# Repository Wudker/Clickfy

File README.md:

# Clickfy – BLE Multimedia Remote

Clickfy is a compact, keychain-sized multimedia remote based on the ESP32-C3. It communicates through the BLE HID profile and provides dedicated controls for play/pause, next track and previous track. A custom PCB integrates the control buttons, Li-Po battery, status LED and battery-voltage monitoring circuit. The firmware uses sleep modes to reduce power consumption, with development focused on minimizing wake-up and BLE reconnection times.

## Technologies

`ESP32-C3` `C/C++` `Bluetooth Low Energy` `BLE HID` `Li-Po battery` `ADC battery monitoring` `Custom PCB` `Low-power operation`

## Usage and development status

After powering on the device, pair Clickfy with a phone, computer or another BLE-compatible media device and use the three buttons to control playback. The current prototype has been built and tested. Planned improvements include further power optimization, shorter reconnection times and support for additional multimedia functions.

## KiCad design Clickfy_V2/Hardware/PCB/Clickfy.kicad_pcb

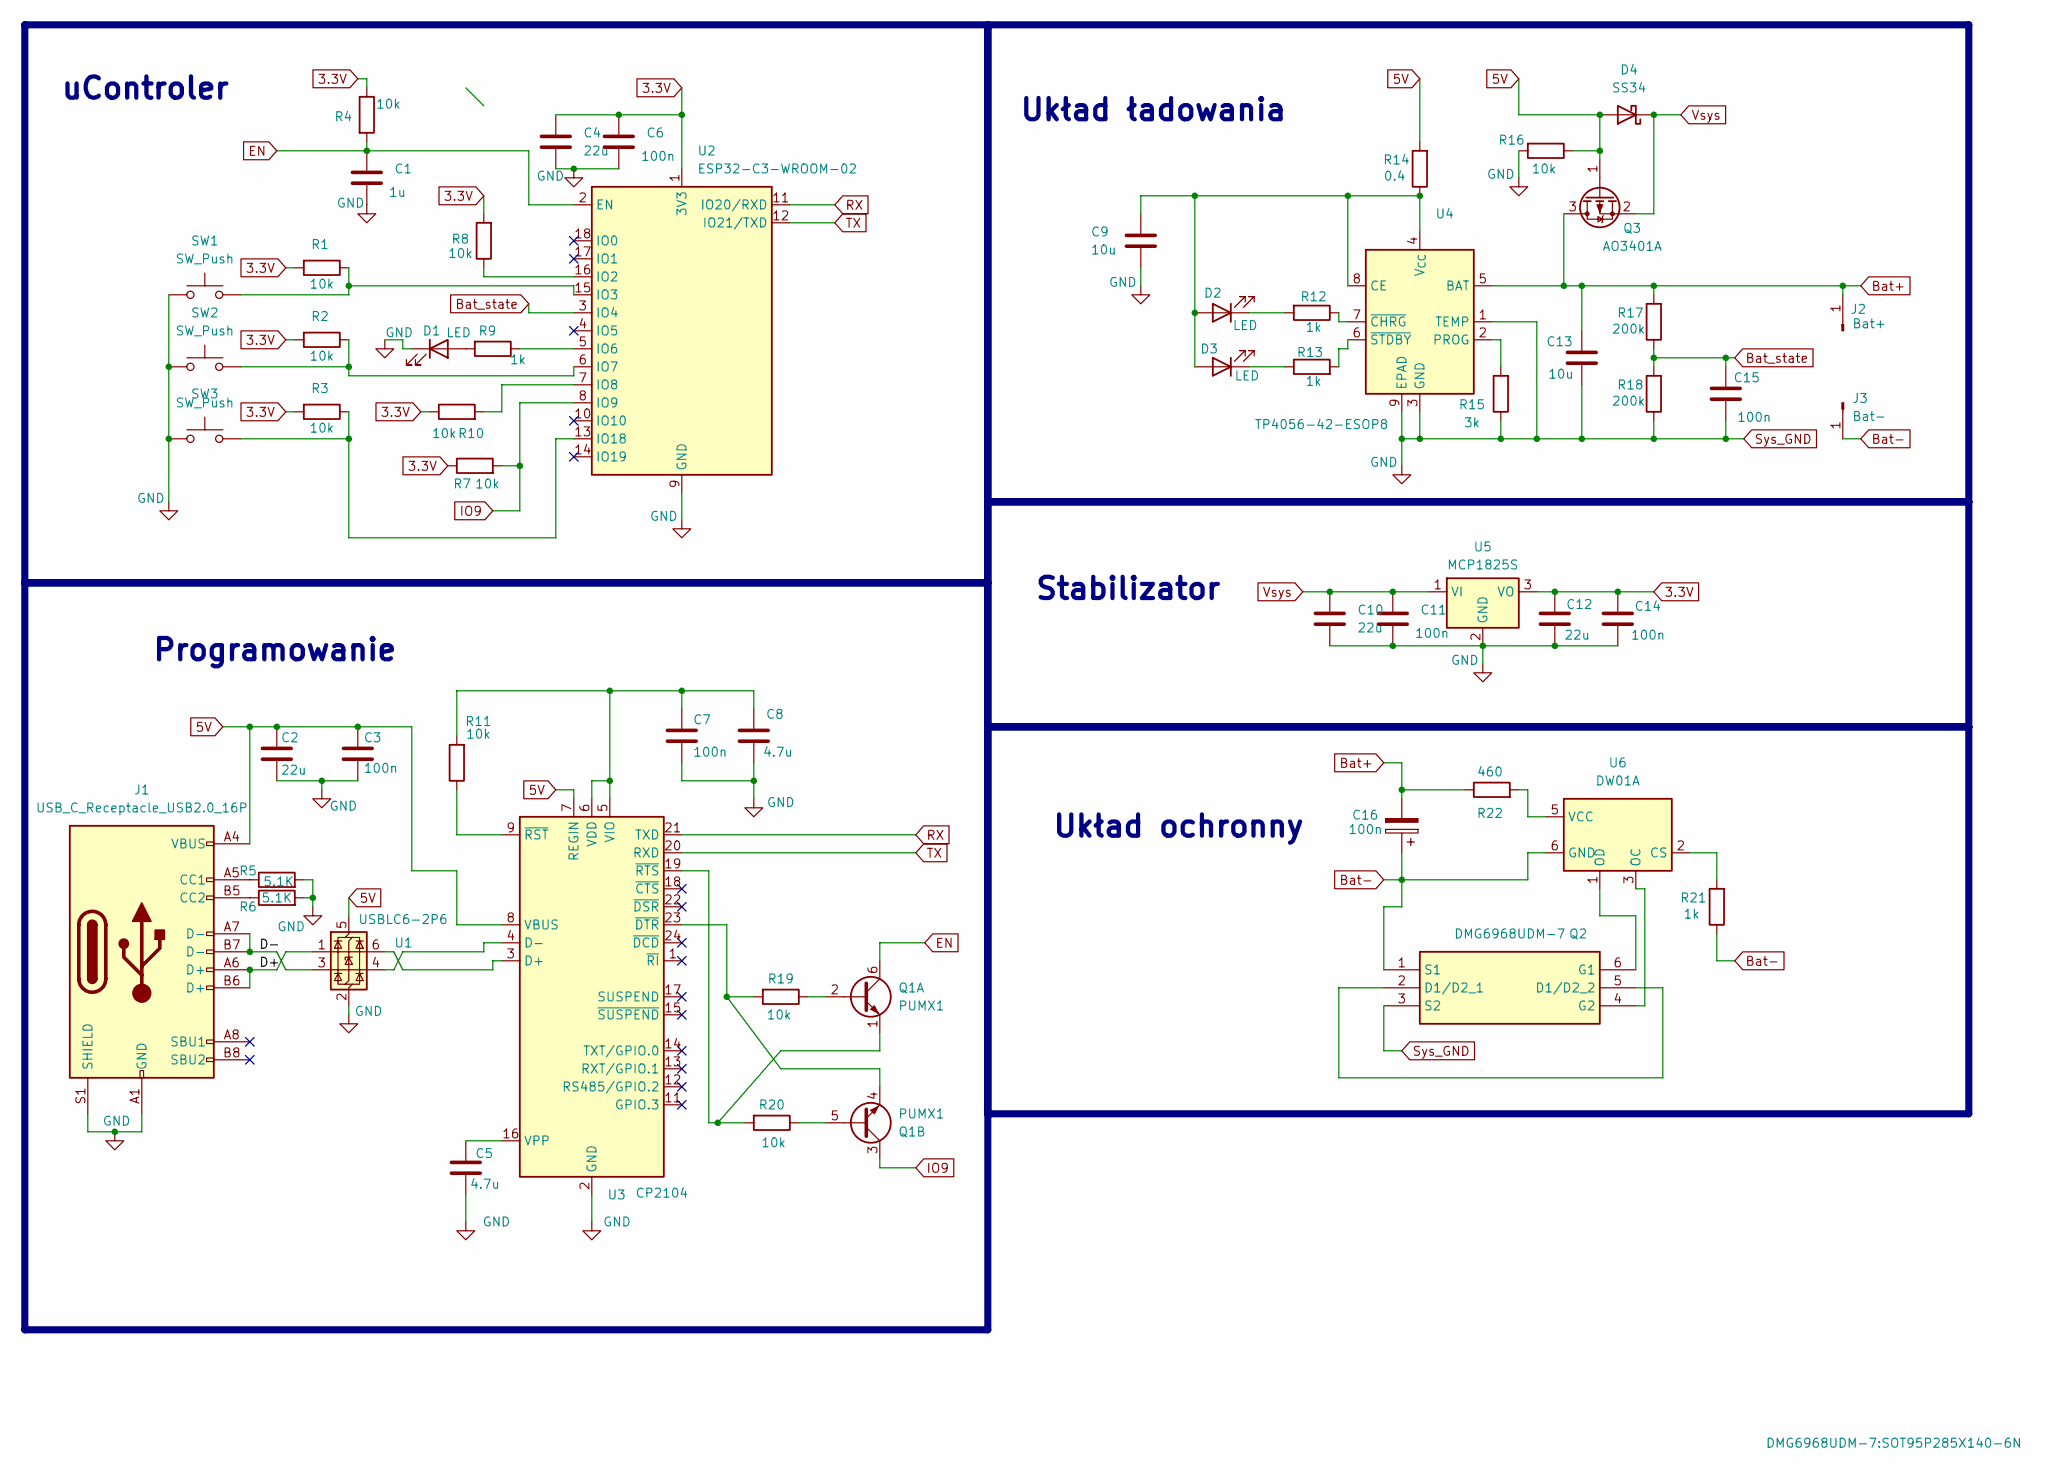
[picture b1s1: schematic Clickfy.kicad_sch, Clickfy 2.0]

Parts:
C1: 1u; C_1206_3216Metric
C2, C4, C10, C12: 22u; C_1206_3216Metric
C3, C6, C7, C11, C14, C15, C16: 100n; C_1206_3216Metric
C5, C8: 4.7u; C_1206_3216Metric
C9, C13: 10u; C_1206_3216Metric
D1: LED; LED_D3.0mm
D2, D3: LED; LED_1206_3216Metric
D4: SS34; D_SMC
J1: USB_C_Receptacle_USB2.0_16P; USB_C_Receptacle_GCT_USB4105-xx-A_16P_TopMnt_Horizontal
J2: Bat+; SolderWire-0.1sqmm_1x01_D0.4mm_OD1mm
J3: Bat-; SolderWire-0.1sqmm_1x01_D0.4mm_OD1mm
Q1: PUMX1; SOT-363_SC-70-6
Q2: DMG6968UDM-7; SOT95P285X140-6N; Manufacturer_Part_Number DMG6968UDM-7
Q3: AO3401A; SOT-23
R1, R2, R3, R4, R7, R8, R10, R11, R16, R19, R20: 10k; R_1206_3216Metric
R5, R6: 5.1K; R_1206_3216Metric
R9, R12, R13, R21: 1k; R_1206_3216Metric
R14: 0.4; R_1206_3216Metric
R15: 3k; R_1206_3216Metric
R17, R18: 200k; R_1206_3216Metric
R22: 460; R_1206_3216Metric
SW1, SW2, SW3: SW_Push; SW_Push_1P1T_NO_E-Switch_TL3301NxxxxxG
U1: USBLC6-2P6; SOT-666
U2: ESP32-C3-WROOM-02
U3: CP2104; QFN-24-1EP_4x4mm_P0.5mm_EP2.6x2.6mm
U4: TP4056-42-ESOP8; HSOP-8-1EP_3.9x4.9mm_P1.27mm_EP2.41x3.1mm
U5: MCP1825S; SOT-223-3_TabPin2
U6: DW01A; SOT-23-6

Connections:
3.3V: C4.1, C6.1, C12.1, C14.1, R1.2, R2.2, R3.2, R4.1, R7.1, R8.2, R10.1, U2.1 (3V3), U5.3 (VO)
5V: C2.1, C3.1, D4.2 (A), J1.A4 (VBUS), J1.A9 (VBUS), J1.B4 (VBUS), J1.B9 (VBUS), Q3.1 (G), R14.2, R16.1, U1.5 (VBUS), U3.7 (REGIN), U3.8 (VBUS)
/D+: J1.A6 (D+), J1.B6 (D+), U1.1 (I/O1)
/D-: J1.A7 (D-), J1.B7 (D-), U1.3 (I/O2)
Bat+: C13.1, C16.2, J2.1, Q3.3 (D), R17.2, R22.1, U4.5 (BAT)
Bat-: C16.1, J3.1, Q2.1 (S1), R21.1, U6.6 (GND)
Bat_state: C15.1, R17.1, R18.2, U2.3 (IO4)
EN: C1.1, Q1.6 (C1), R4.2, U2.2 (EN)
IO9: Q1.3 (C2), R7.2, U2.8 (IO9)
unnamed: D1.2 (A), R9.2
unnamed: C9.1, D2.2 (A), D3.2 (A), R14.1, U4.4 (V_{CC}), U4.8 (CE)
unnamed: D2.1 (K), R12.2
unnamed: D3.1 (K), R13.1
unnamed: J1.A5 (CC1), R5.1
unnamed: J1.B5 (CC2), R6.1
unnamed: Q1.2 (B1), R19.1
unnamed: Q1.1 (E1), R20.2, U3.19 (~RTS)
unnamed: Q1.5 (B2), R20.1
unnamed: Q1.4 (E2), R19.2, U3.23 (~DTR)
unnamed: Q2.2 (D1/D2_1), Q2.5 (D1/D2_2)
unnamed: Q2.6 (G1), U6.1 (OD)
unnamed: Q2.4 (G2), U6.3 (OC)
unnamed: R8.1, U2.16 (IO2)
unnamed: R1.1, SW1.2, U2.15 (IO3)
unnamed: R9.1, U2.5 (IO6)
unnamed: R2.1, SW2.2, U2.6 (IO7)
unnamed: R10.2, U2.7 (IO8)
unnamed: R3.1, SW3.2, U2.13 (IO18)
unnamed: U1.6 (I/O1), U3.3 (D+)
unnamed: U1.4 (I/O2), U3.4 (D-)
unnamed: C7.1, C8.2, R11.2, U3.5 (VIO), U3.6 (VDD)
unnamed: C5.1, U3.16 (VPP)
unnamed: R11.1, U3.9 (~RST)
unnamed: R15.2, U4.2 (PROG)
unnamed: R12.1, U4.7 (~CHRG)
unnamed: R13.2, U4.6 (~STDBY)
unnamed: R21.2, U6.2 (CS)
unnamed: R22.2, U6.5 (VCC)
RX: U2.11 (IO20/RXD), U3.21 (TXD)
Sys_GND: C1.2, C2.2, C3.2, C4.2, C5.2, C6.2, C7.2, C8.1, C9.2, C10.2, C11.2, C12.2, C13.2, C14.2, C15.2, D1.1 (K), J1.A1 (GND), J1.A12 (GND), J1.B1 (GND), J1.B12 (GND), J1.S1 (SHIELD), Q2.3 (S2), R5.2, R6.2, R15.1, R16.2, R18.1, SW1.1, SW2.1, SW3.1, U1.2 (GND), U2.9 (GND), U2.19 (GND), U3.2 (GND), U3.25 (GND), U4.1 (TEMP), U4.3 (GND), U4.9 (EPAD), U5.2 (GND)
TX: U2.12 (IO21/TXD), U3.20 (RXD)
Vsys: C10.1, C11.1, D4.1 (K), Q3.2 (S), U5.1 (VI)

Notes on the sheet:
Stabilizator
Programowanie
uControler
Układ ładowania
Układ ochronny

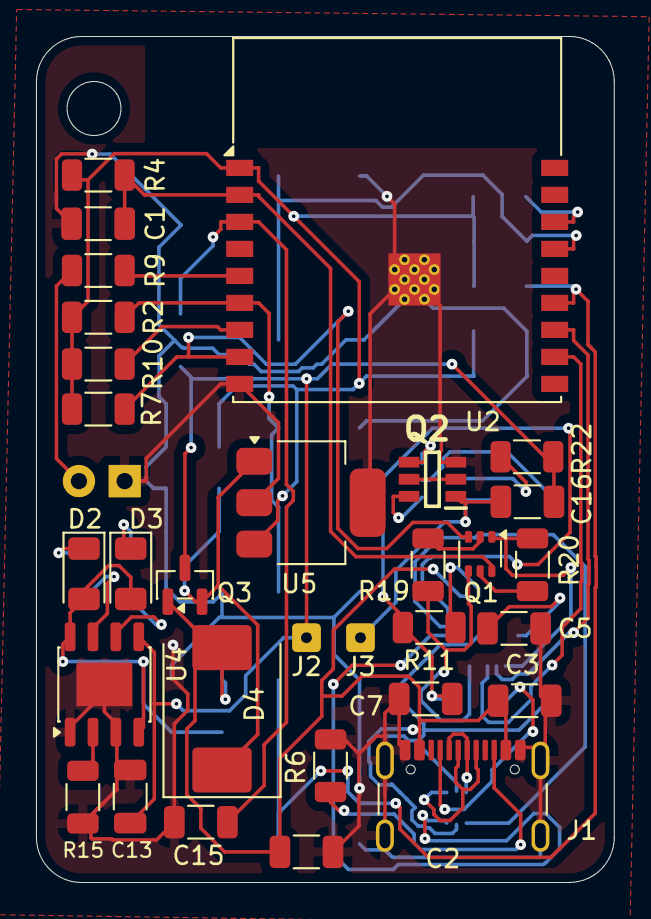
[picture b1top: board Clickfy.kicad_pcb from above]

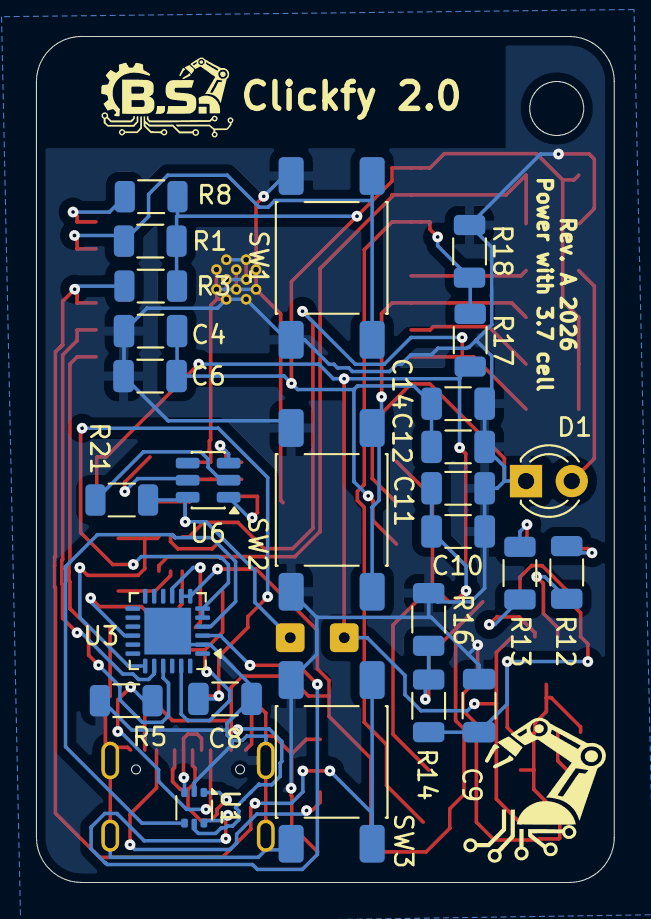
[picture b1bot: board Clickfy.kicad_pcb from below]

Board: 2 copper layers, 32.1 x 47.0 mm, 57 parts (26 on the bottom side), 42 nets.

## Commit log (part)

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2026-05-23 Revise README with detailed project information
    Expanded project description, added features, hardware, software, challenges, and current status sections to README.
2026-05-23 Create PCB
